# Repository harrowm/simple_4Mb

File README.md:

# simple_4Mb
A simple 4Mb RAM expansion card for the rosco sac.  Complicated only by the fact its mainly SMT ...

24th Feb 2025

The boards are back from jlcpcb.  The only potential issue is that I put the vias for the capacitors on the pad.  This seems to have worked by default without the expensive via in pad process.  The connections between the pads and VCC/GND check out ok.

Running on the 68030 rosco works fine!

.. but the board is struggling on the 68010, not sure why ?

11th Feb 2025 - Sent to jlcpcb

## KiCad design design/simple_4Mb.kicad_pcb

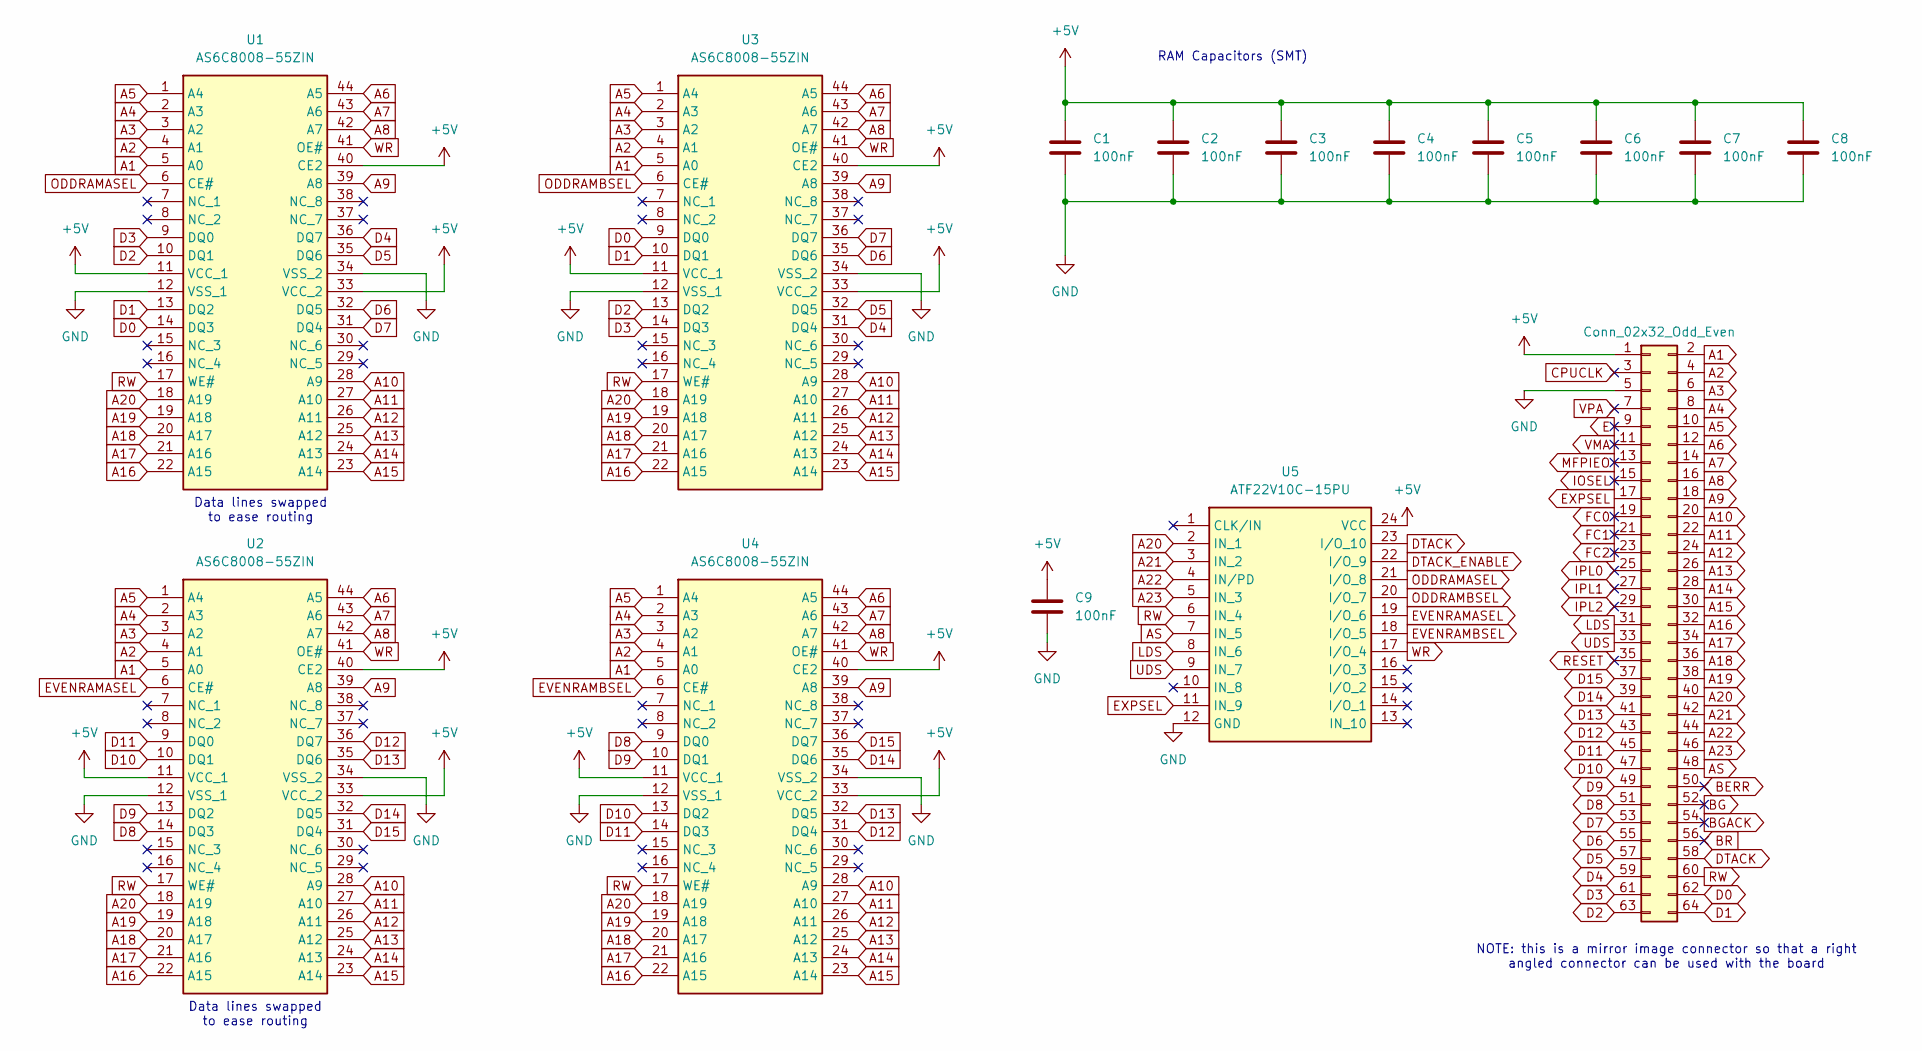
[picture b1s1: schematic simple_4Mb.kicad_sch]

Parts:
BUS1: Conn_02x32_Odd_Even; PinHeader_2x32_P2.54mm_Vertical
C1, C2, C3, C4, C5, C6, C7, C8, C9: 100nF; C_0805_2012Metric_Pad1.18x1.45mm_HandSolder
U1, U2, U3, U4: AS6C8008-55ZIN; TSOP-II-44_10.16x18.41mm_P0.8mm; Manufacturer_Part_Number AS6C8008-55ZIN; Mouser Part Number 913-AS6C8008-55ZIN
U5: ATF22V10C-15PU; DIP-24_W7.62mm_Socket_LongPads; Mouser Part Number 556-AF22V10C15PU

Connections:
+5V: BUS1.1, C1.1, C2.1, C3.1, C4.1, C5.1, C6.1, C7.1, C8.1, C9.1, U1.11 (VCC_1), U1.33 (VCC_2), U1.40 (CE2), U2.11 (VCC_1), U2.33 (VCC_2), U2.40 (CE2), U3.11 (VCC_1), U3.33 (VCC_2), U3.40 (CE2), U4.11 (VCC_1), U4.33 (VCC_2), U4.40 (CE2), U5.24 (VCC)
A1: BUS1.2, U1.5 (A0), U2.5 (A0), U3.5 (A0), U4.5 (A0)
A2: BUS1.4, U1.4 (A1), U2.4 (A1), U3.4 (A1), U4.4 (A1)
A3: BUS1.6, U1.3 (A2), U2.3 (A2), U3.3 (A2), U4.3 (A2)
A4: BUS1.8, U1.2 (A3), U2.2 (A3), U3.2 (A3), U4.2 (A3)
A5: BUS1.10, U1.1 (A4), U2.1 (A4), U3.1 (A4), U4.1 (A4)
A6: BUS1.12, U1.44 (A5), U2.44 (A5), U3.44 (A5), U4.44 (A5)
A7: BUS1.14, U1.43 (A6), U2.43 (A6), U3.43 (A6), U4.43 (A6)
A8: BUS1.16, U1.42 (A7), U2.42 (A7), U3.42 (A7), U4.42 (A7)
A9: BUS1.18, U1.39 (A8), U2.39 (A8), U3.39 (A8), U4.39 (A8)
A10: BUS1.20, U1.28 (A9), U2.28 (A9), U3.28 (A9), U4.28 (A9)
A11: BUS1.22, U1.27 (A10), U2.27 (A10), U3.27 (A10), U4.27 (A10)
A12: BUS1.24, U1.26 (A11), U2.26 (A11), U3.26 (A11), U4.26 (A11)
A13: BUS1.26, U1.25 (A12), U2.25 (A12), U3.25 (A12), U4.25 (A12)
A14: BUS1.28, U1.24 (A13), U2.24 (A13), U3.24 (A13), U4.24 (A13)
A15: BUS1.30, U1.23 (A14), U2.23 (A14), U3.23 (A14), U4.23 (A14)
A16: BUS1.32, U1.22 (A15), U2.22 (A15), U3.22 (A15), U4.22 (A15)
A17: BUS1.34, U1.21 (A16), U2.21 (A16), U3.21 (A16), U4.21 (A16)
A18: BUS1.36, U1.20 (A17), U2.20 (A17), U3.20 (A17), U4.20 (A17)
A19: BUS1.38, U1.19 (A18), U2.19 (A18), U3.19 (A18), U4.19 (A18)
A20: BUS1.40, U1.18 (A19), U2.18 (A19), U3.18 (A19), U4.18 (A19), U5.2 (IN_1)
A21: BUS1.42, U5.3 (IN_2)
A22: BUS1.44, U5.4 (IN/PD)
A23: BUS1.46, U5.5 (IN_3)
AS: BUS1.48, U5.7 (IN_5)
BERR: BUS1.50
BG: BUS1.52
BGACK: BUS1.54
BR: BUS1.56
CPUCLK: BUS1.3
D0: BUS1.62, U1.14 (DQ3), U3.9 (DQ0)
D1: BUS1.64, U1.13 (DQ2), U3.10 (DQ1)
D2: BUS1.63, U1.10 (DQ1), U3.13 (DQ2)
D3: BUS1.61, U1.9 (DQ0), U3.14 (DQ3)
D4: BUS1.59, U1.36 (DQ7), U3.31 (DQ4)
D5: BUS1.57, U1.35 (DQ6), U3.32 (DQ5)
D6: BUS1.55, U1.32 (DQ5), U3.35 (DQ6)
D7: BUS1.53, U1.31 (DQ4), U3.36 (DQ7)
D8: BUS1.51, U2.14 (DQ3), U4.9 (DQ0)
D9: BUS1.49, U2.13 (DQ2), U4.10 (DQ1)
D10: BUS1.47, U2.10 (DQ1), U4.13 (DQ2)
D11: BUS1.45, U2.9 (DQ0), U4.14 (DQ3)
D12: BUS1.43, U2.36 (DQ7), U4.31 (DQ4)
D13: BUS1.41, U2.35 (DQ6), U4.32 (DQ5)
D14: BUS1.39, U2.32 (DQ5), U4.35 (DQ6)
D15: BUS1.37, U2.31 (DQ4), U4.36 (DQ7)
DTACK: BUS1.58, U5.23 (I/O_10)
DTACK_ENABLE: U5.22 (I/O_9)
E: BUS1.9
EVENRAMASEL: U2.6 (CE#), U5.19 (I/O_6)
EVENRAMBSEL: U4.6 (CE#), U5.18 (I/O_5)
EXPSEL: BUS1.17, U5.11 (IN_9)
FC0: BUS1.19
FC1: BUS1.21
FC2: BUS1.23
GND: BUS1.5, C1.2, C2.2, C3.2, C4.2, C5.2, C6.2, C7.2, C8.2, C9.2, U1.12 (VSS_1), U1.34 (VSS_2), U2.12 (VSS_1), U2.34 (VSS_2), U3.12 (VSS_1), U3.34 (VSS_2), U4.12 (VSS_1), U4.34 (VSS_2), U5.12 (GND)
IOSEL: BUS1.15
IPL0: BUS1.25
IPL1: BUS1.27
IPL2: BUS1.29
LDS: BUS1.31, U5.8 (IN_6)
MFPIEO: BUS1.13
ODDRAMASEL: U1.6 (CE#), U5.21 (I/O_8)
ODDRAMBSEL: U3.6 (CE#), U5.20 (I/O_7)
RESET: BUS1.35
RW: BUS1.60, U1.17 (WE#), U2.17 (WE#), U3.17 (WE#), U4.17 (WE#), U5.6 (IN_4)
UDS: BUS1.33, U5.9 (IN_7)
VMA: BUS1.11
VPA: BUS1.7
WR: U1.41 (OE#), U2.41 (OE#), U3.41 (OE#), U4.41 (OE#), U5.17 (I/O_4)

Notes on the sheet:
NOTE: this is a mirror image connector so that a right angled connector can be used with the board
Data lines swapped to ease routing
RAM Capacitors (SMT)

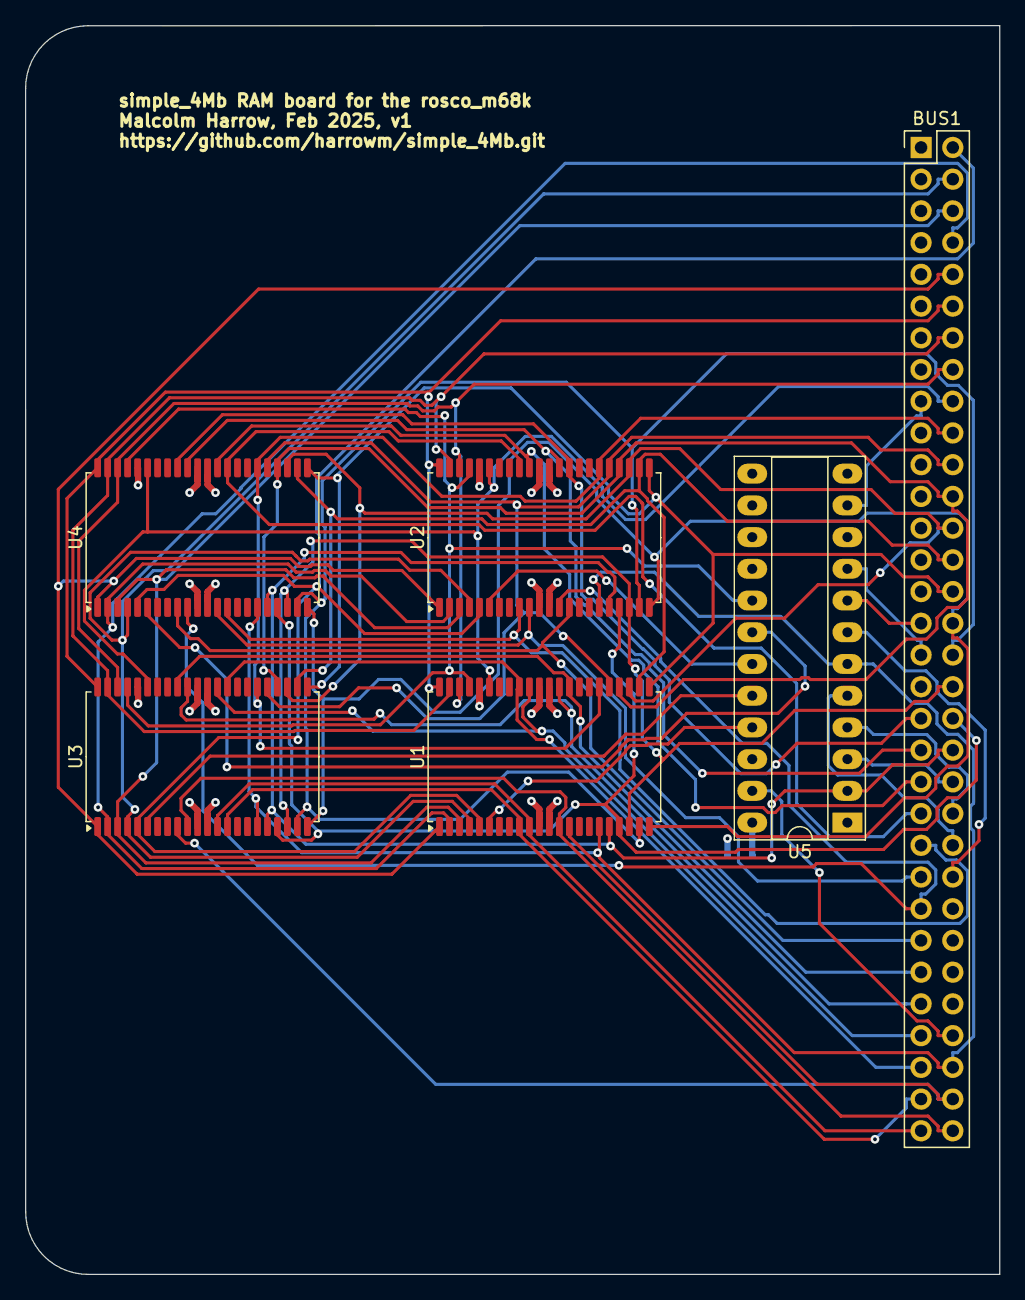
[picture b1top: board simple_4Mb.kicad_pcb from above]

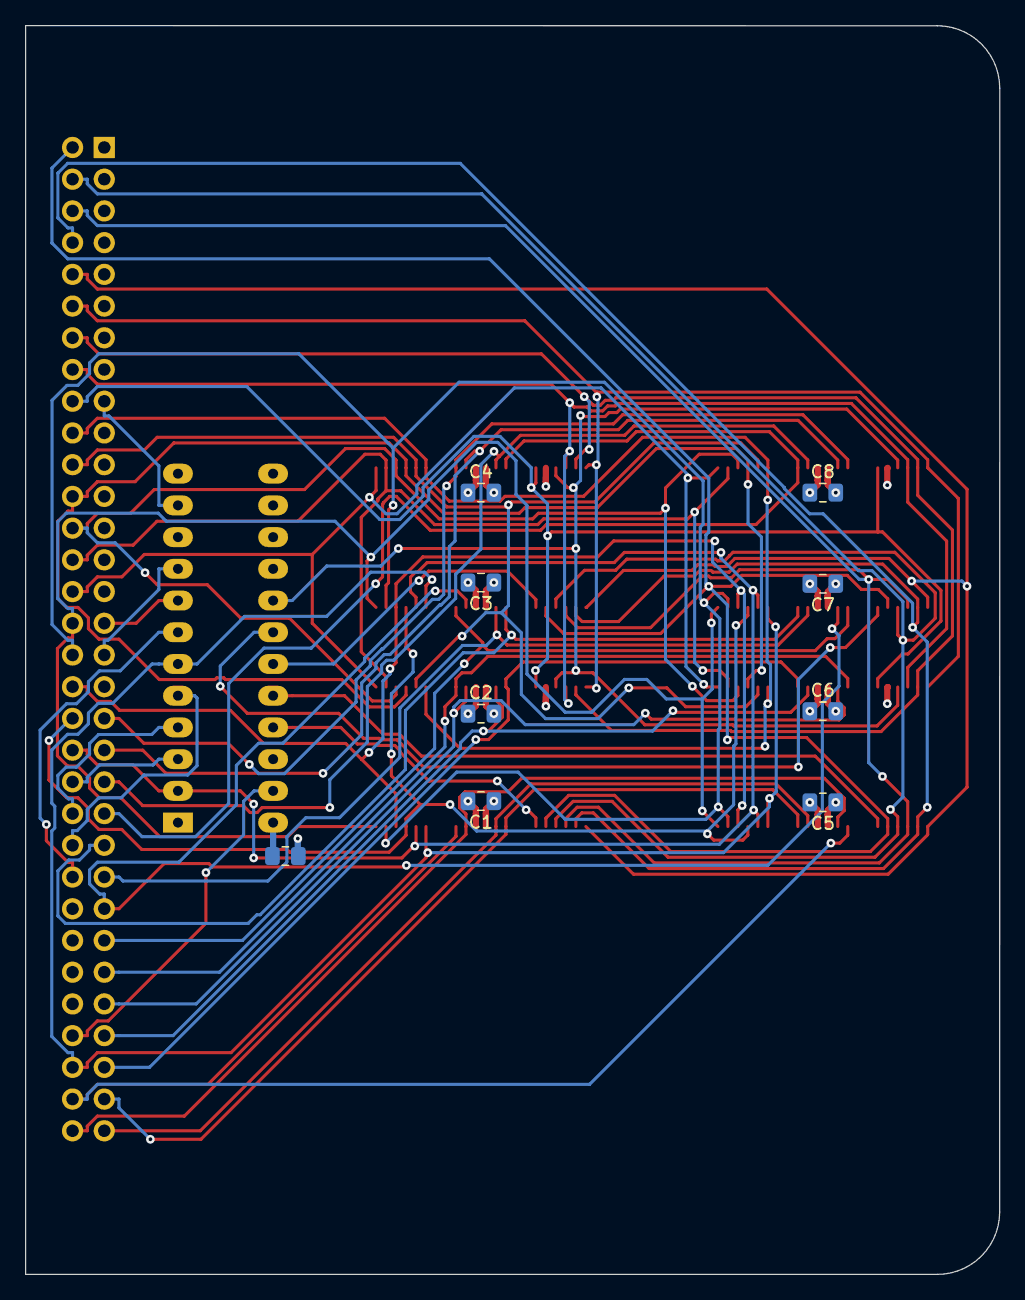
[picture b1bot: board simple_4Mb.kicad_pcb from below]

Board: 4 copper layers, 78.0 x 100.0 mm, 15 parts (9 on the bottom side), 52 nets.

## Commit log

2025-02-11 Initial cupl for decoder
2025-02-11 Initial board design
2025-02-11 Add datasheet for memory and production data
2025-02-11 Add pictures to readme
2025-02-11 Update readme images
2025-02-24 Update after first build
2025-02-25 Correct comment about not handling DTACK
2025-02-26 Added docs
